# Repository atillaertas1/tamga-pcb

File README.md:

<p align="center">
  <picture>
    <source media="(prefers-color-scheme: dark)" srcset="assets/logo-dark.svg" />
    
  </picture>
</p>

<p align="center"><b>Describe a circuit. Get a routed, DRC-clean KiCad board and a JLCPCB order.</b></p>

<p align="center">
  
  &nbsp;
  
  &nbsp;
  
  &nbsp;
  
  &nbsp;
  
  &nbsp;
  
</p>

<p align="center"><sub>An ESP32-C3 board with USB-C, a 3.3 V regulator, reset/boot buttons and a GPIO header: schematic,
placement, routing, ground pour, DRC and fab files all made through tamga-pcb's tools.
<a href="examples/esp32c3-devboard">Rebuild it yourself</a>.</sub></p>

**tamga-pcb** gives Claude Code the whole KiCad workflow as 22 compact tools. You describe the board in plain
words; Claude writes a short circuit spec, tamga-pcb turns it into a schematic and a PCB, places the parts,
routes the board with Freerouting, pours ground, loops on DRC until it is clean, and exports Gerbers, BOM and
pick-and-place for JLCPCB. Every LCSC part is checked against its real pinout on the way, and Claude never reads
raw KiCad files: tools answer in one-line summaries, so a whole board fits comfortably in the context.

```
> Make me an ESP32-C3 board powered from USB-C, with reset and boot buttons, a user LED
  and a GPIO header. Keep it under 60 x 32 mm and get it ready for JLCPCB.
```

## Examples

<table>
  <tr>
    <td width="50%" align="center"></td>
    <td width="50%" align="center"></td>
  </tr>
  <tr>
    <td><b><a href="examples/ch340-usb-uart">CH340C USB-C to UART adapter</a></b><br/><sub>Made by Claude Code from <b>one
    prompt</b>, unattended: 35 × 20 mm, DRC clean, fab files. <b>3 min, 48 tool calls, about $0.51</b> with Sonnet 5.5,
    measured. <a href="examples/ch340-usb-uart/SESSION.md">Session report</a></sub></td>
    <td><b><a href="examples/esp32c3-devboard">ESP32-C3 USB-C dev board</a></b><br/><sub>60 × 32 mm, 19 parts, reset/boot,
    native USB. Rebuilt end to end by a script through the same tools; the reference for the images above.</sub></td>
  </tr>
</table>

Token counts, cost, time and what the first attempt taught us: [docs/BENCHMARKS.md](docs/BENCHMARKS.md). On the same prompt with the same model, the most-starred KiCad MCP server also finished the board; tamga-pcb used 48 % less money, 43 % fewer tool calls and 40 % less peak context (one run each, [details](docs/BENCHMARKS.md#against-another-kicad-mcp-server)).

## Watch it live

Say *"I want to watch"* and Claude calls `live_view`: a page opens in your browser and redraws the board and the
schematic after every step, with each tool call, how long it took and what it found, and the DRC status on top.
It runs locally, needs no KiCad window, and costs no tokens: none of it goes back to Claude. From a terminal:
`uv run tamga watch` follows whatever project Claude is working on.

<p align="center"><sub>Replay of a real, unattended session: one prompt (an ATtiny85 board with USB-C, LDO, ISP header and
three LEDs, rounded corners, mounting holes), 59 tool calls, 5½ minutes, $0.68 with Sonnet 5.5. Every frame is one of
the session's own board states, made with <a href="scripts/replay_gif.py"><code>scripts/replay_gif.py</code></a>.</sub></p>

## Install

Run this inside Claude Code:

```
/plugin install tamga-pcb --marketplace atillaertas1/tamga-pcb
```

You need **[KiCad 10](https://www.kicad.org/download/)** and **[uv](https://docs.astral.sh/uv/)**; autorouting
also needs **Java 25+**. tamga-pcb finds KiCad on its own on Linux, macOS and Windows, builds its Python
environment on first start and downloads Freerouting the first time it routes. No API keys.

<details>
<summary>Older Claude Code versions</summary>

```
/plugin marketplace add atillaertas1/tamga-pcb
/plugin install tamga-pcb@tamga-pcb
```

</details>

<details>
<summary>Other MCP clients</summary>

Clone the repo and register this as a stdio server:

```bash
uv run --directory /path/to/tamga-pcb --extra lcsc tamga
```

The design workflow the plugin loads as a skill lives in [`skills/pcb-design/SKILL.md`](skills/pcb-design/SKILL.md);
give it to your agent as instructions.

</details>

<details>
<summary>Something not found?</summary>

Ask Claude to *run the tamga doctor*. It checks KiCad, its Python, the libraries, Java and the network, and names the
environment variable to set for anything it cannot find: `TAMGA_KICAD_CLI`, `TAMGA_KICAD_PYTHON`,
`TAMGA_SYMBOL_DIR`, `TAMGA_FOOTPRINT_DIR`, `TAMGA_JAVA`, `FREEROUTING_JAR`.

</details>

## From a spec to a board

The single source of truth is a short `<name>.circuit.json`: parts, footprints, LCSC numbers and which net each
pin goes to. Claude writes it, tamga-pcb does the rest.

```json
{"ref": "U2", "symbol": "RF_Module:ESP32-C3-WROOM-02", "lcsc": "C2934560",
 "footprint": "RF_Module:ESP32-C3-WROOM-02", "sheet": "MCU",
 "pins": {"1": "+3V3", "2": "EN", "13": "USB_DN", "14": "USB_DP", "9": "GND"}}
```

<table>
  <tr>
    <td width="50%"></td>
    <td width="50%"></td>
  </tr>
  <tr>
    <td align="center"><sub>Generated schematic, one sheet per function</sub></td>
    <td align="center"><sub>Autorouted copper before the ground pour</sub></td>
  </tr>
</table>

## How it works

1. **Spec → schematic.** `sync_design` writes the `.kicad_sch` (functional sheets, power symbols, notes,
   deterministic UUIDs), exports the netlist with `kicad-cli` and checks it against the spec. A wrong pin name or a
   missing pad writes nothing and lists the valid pins.
2. **Check the real parts.** Each LCSC number is compared with the part's EasyEDA pinout. A swapped LED or the wrong
   symbol variant shows up here, not on the assembled board.
3. **Schematic → PCB.** The board is updated from the netlist like KiCad's *Update PCB*, keeping placement, then ERC
   and a schematic↔PCB parity check run.
4. **Place and route.** Claude places the parts in one batch, widens power nets with netclasses, hand-routes critical
   nets with `route_net` (locked), and lets Freerouting route the rest headlessly.
5. **Pour and verify.** A two-layer ground pour with stitching vias, then `run_drc` until it says `CLEAN`, with the
   violations grouped by type and located.
6. **Order.** `export_fab` writes Gerbers, drill files, a BOM and a CPL in JLCPCB's format and lists parts without an
   LCSC code.

The [pcb-design skill](skills/pcb-design/SKILL.md) carries the loop, the placement checklist and JLCPCB's limits, so
Claude follows the same steps every time.

## The tools

| Tool | What it does |
| --- | --- |
| `sync_design` | Spec → schematic + PCB, netlist and pinout checks, ERC, parity. Edits go through small patches. |
| `find_symbol`, `get_symbol`, `find_footprint` | Search KiCad's libraries; confirm pin names and that footprint pads match. |
| `search_parts`, `import_lcsc_part` | JLCPCB/LCSC stock and price, basic parts first, passives by value; bring in parts KiCad doesn't have. |
| `create_part` | Footprint and symbol from a datasheet when neither KiCad nor LCSC has the part: SOIC/TSSOP/MSOP, QFN/DFN, headers, custom pads. |
| `board_summary`, `get_footprint` | One line per footprint and net, pad positions, routed lengths and pair skew. No raw `.kicad_pcb` in the context. |
| `place_footprints` | Move, rotate and flip many footprints in one call. |
| `set_netclass`, `route_net` | Track widths per net class, sized from a target impedance; guided, locked routes and differential pairs. |
| `autoroute` | Freerouting without its GUI, with progress and a timeout that reports where it stopped. |
| `add_copper_zone`, `fill_zones` | Ground pours with stitching vias. |
| `run_drc`, `run_erc` | Violations grouped by type with example locations: 300 violations fit in about 1 KB. |
| `render_board` | PNG of the board for a visual check. |
| `live_view` | Opens the live page for the user (above); nothing comes back to Claude. |
| `export_fab` | Gerbers, drill, BOM and CPL for JLCPCB; optional schematic PDF, STEP, ODB++, IPC-2581 and a parts-cost summary. |
| `import_board` | Bring in Altium, Eagle, PADS or CADSTAR boards. |

## Why it is cheap on tokens

| Choice | Effect |
| --- | --- |
| 22 tools with short descriptions | all tool schemas together ≈ 4.2k tokens (16.7k characters, measured) |
| Small answers | in the [CH340 run](examples/ch340-usb-uart/SESSION.md) all 48 tool results together were ≈ 4.2k tokens, about 350 characters per call |
| No raw KiCad files, one line per footprint | a 7-part board summary is about 900 characters |
| DRC/ERC grouped by type, three example locations | 300 violations → about 1 KB |
| Workflow in a skill | loaded only when you work on a PCB |

## Under the hood

- **pcbnew runs in a worker process** in KiCad's own Python; it can crash without taking the server down.
- **File based**, not KiCad's IPC API: it works without the KiCad window open, and in CI.
- **Freerouting through pcbnew's DSN/SES export**, because `kicad-cli` 10 has none.
- **Self-contained projects:** non-stock libraries are copied into `<project>/lib/`, so a project folder can be zipped
  and shared as is.

## Development

```bash
git clone https://github.com/atillaertas1/tamga-pcb && cd tamga-pcb
uv sync --extra lcsc
uv run pytest -q          # KiCad-dependent tests are skipped when KiCad is not installed
claude --plugin-dir .     # run Claude Code with your working copy as the plugin
```

The example board is rebuilt end to end by `uv run python examples/esp32c3-devboard/build.py`. Changes are listed in
the [changelog](CHANGELOG.md). Want to help? See [CONTRIBUTING.md](CONTRIBUTING.md) and the
[good first issues](https://github.com/atillaertas1/tamga-pcb/labels/good%20first%20issue).

## Roadmap

- [ ] Live editing in an open KiCad through its IPC API
- [ ] Hierarchical pins on sheet symbols, tidier power-sheet layout
- [ ] Alternative routers (DeepPCB, Quilter)
- [ ] ngspice simulation of analog blocks

## The name

A *tamga* is the seal Turkic clans stamped onto stone, metal and coins: a mark pressed permanently into a surface,
much like a circuit etched into copper.

## License

MIT, see [LICENSE](LICENSE). **The boards you make are entirely yours**; no tool's license carries over to its output.
Optional parts are installed separately under their own licenses: easyeda2kicad (AGPL-3.0, the `lcsc` extra, run as a
separate process) and Freerouting (GPL-3.0, a separate jar downloaded on first use). KiCad is GPL-3.0.

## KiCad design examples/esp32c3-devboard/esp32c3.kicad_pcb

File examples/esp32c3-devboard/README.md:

# ESP32-C3 USB-C dev board

A 60 × 32 mm, two-layer board made entirely through tamga-pcb's tools, the same calls Claude makes:

- **USB-C** sink (5.1 kΩ on CC1/CC2), native USB to the ESP32-C3 (IO18 = D−, IO19 = D+)
- **AMS1117-3.3** regulator with input/output capacitors and a power LED
- **ESP32-C3-WROOM-02** module, antenna flush with the board edge
- **Reset and boot** buttons, EN RC delay, IO2/IO8/IO9 strapping
- **10-pin header:** 3V3, GND, UART and five GPIOs, plus VBUS

Every part has a JLCPCB/LCSC number except the header (`missing_lcsc: J2`).

## Files

| File | What it is |
| --- | --- |
| [`esp32c3.circuit.json`](esp32c3.circuit.json) | The spec: the only file written by hand (by Claude) |
| `esp32c3*.kicad_sch` | Generated schematic: Power, MCU and IO sheets |
| `esp32c3.kicad_pcb` | Placed, routed, poured and DRC-clean board |
| [`build.py`](build.py) | Rebuilds everything above from the spec and renders the README images |

## Rebuild

From the repo root, with KiCad 10, Java 25+ and `uv sync --extra lcsc` done:

```bash
uv run python examples/esp32c3-devboard/build.py
```

It runs `sync_design → place_footprints → set_netclass → autoroute → add_copper_zone → run_drc → export_fab`
and stops if DRC is not clean. Freerouting is not deterministic, so the tracks differ from run to run; DRC is clean
either way. The fab package lands in `fab/` (Gerber zip, BOM.csv, CPL.csv).

Two things worth knowing:

- KiCad ships no 3D body for the HRO TYPE-C-31-M-12 USB-C connector, so the render borrows the GCT USB4105 body,
  which has the same outline and locating holes. This only affects the picture.
- `pinout_warnings` from `sync_design` for J1, U1 and the buttons are naming differences between KiCad and EasyEDA
  (merged `A1B12` pins, the regulator tab, the switch's extra pins). The check exists for the real mistakes: on the
  first try it caught a red LED whose LCSC part has pad 1 as the anode while KiCad's footprint has it as the
  cathode, and that LED was swapped for one that matches.

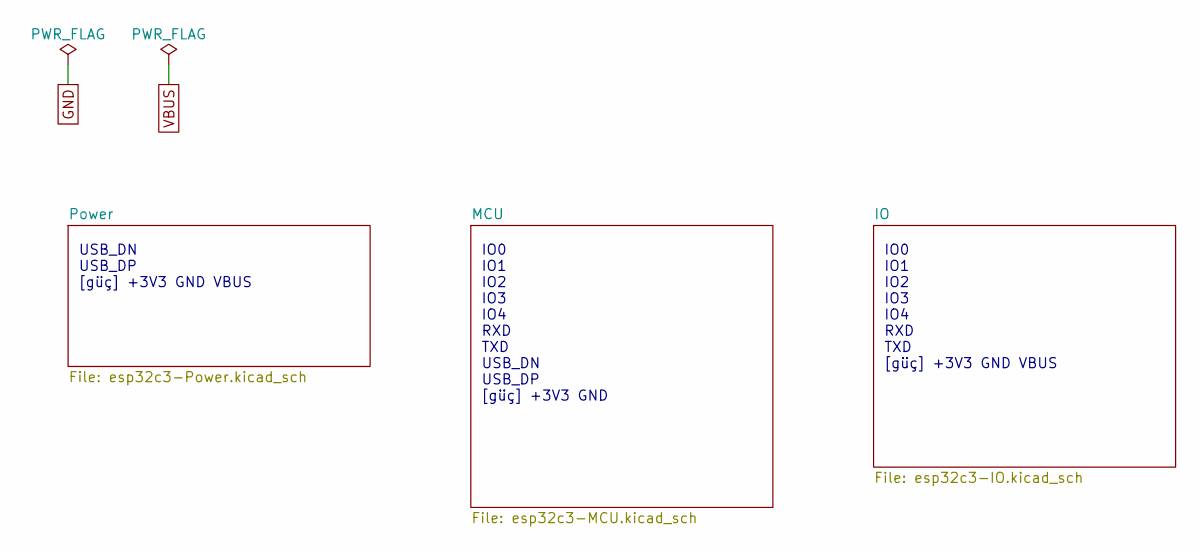
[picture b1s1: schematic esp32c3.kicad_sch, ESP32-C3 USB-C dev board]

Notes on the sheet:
USB_DN USB_DP [güç] +3V3 GND VBUS
IO0 IO1 IO2 IO3 IO4 RXD TXD USB_DN USB_DP [güç] +3V3 GND
IO0 IO1 IO2 IO3 IO4 RXD TXD [güç] +3V3 GND VBUS

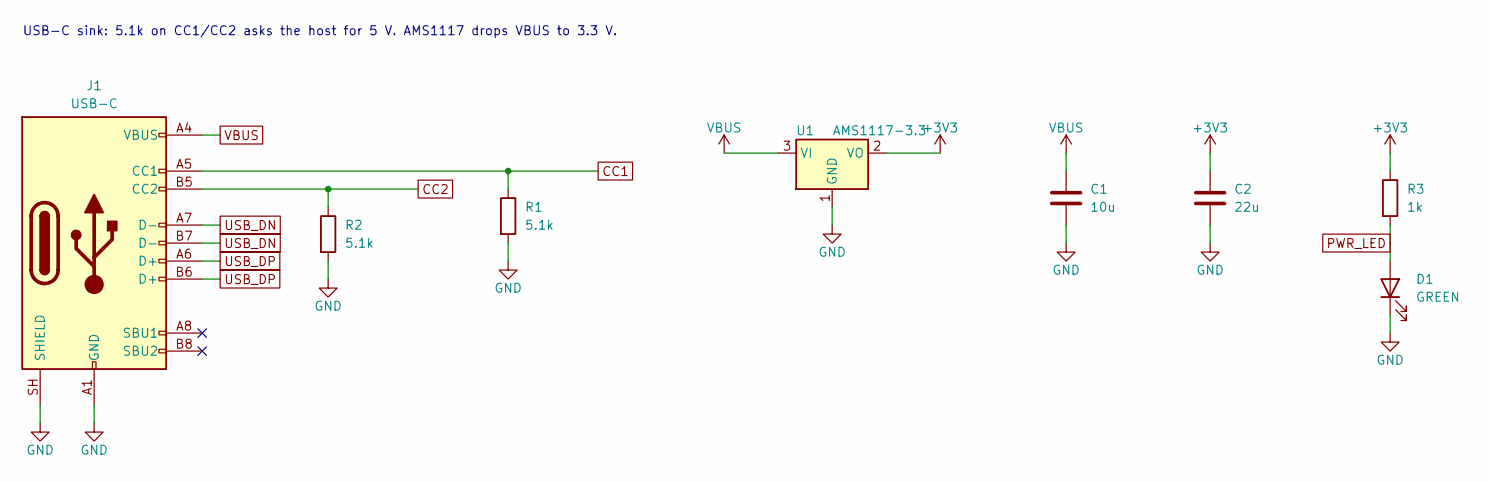
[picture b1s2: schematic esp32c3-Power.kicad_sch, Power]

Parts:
C1: 10u; C_0805_2012Metric; LCSC C15850
C2: 22u; C_0805_2012Metric; LCSC C45783
D1: GREEN; LED_0603_1608Metric; LCSC C72043
J1: USB-C; USB_C_Receptacle_HRO_TYPE-C-31-M-12; LCSC C165948
R1, R2: 5.1k; R_0603_1608Metric; LCSC C23186
R3: 1k; R_0603_1608Metric; LCSC C21190
U1: AMS1117-3.3; SOT-223-3_TabPin2; LCSC C6186

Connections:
+3V3: C2.1, R3.1, U1.2 (VO); also elsewhere on the board
CC1: J1.A5 (CC1), R1.1
CC2: J1.B5 (CC2), R2.1
GND: C1.2, C2.2, D1.1 (K), J1.A1 (GND), J1.A12 (GND), J1.B1 (GND), J1.B12 (GND), J1.SH (SHIELD), R1.2, R2.2, U1.1 (GND); also elsewhere on the board
PWR_LED: D1.2 (A), R3.2
USB_DN: J1.A7 (D-), J1.B7 (D-); also elsewhere on the board
USB_DP: J1.A6 (D+), J1.B6 (D+); also elsewhere on the board
VBUS: C1.1, J1.A4 (VBUS), J1.A9 (VBUS), J1.B4 (VBUS), J1.B9 (VBUS), U1.3 (VI); also elsewhere on the board

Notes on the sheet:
USB-C sink: 5.1k on CC1/CC2 asks the host for 5 V. AMS1117 drops VBUS to 3.3 V.

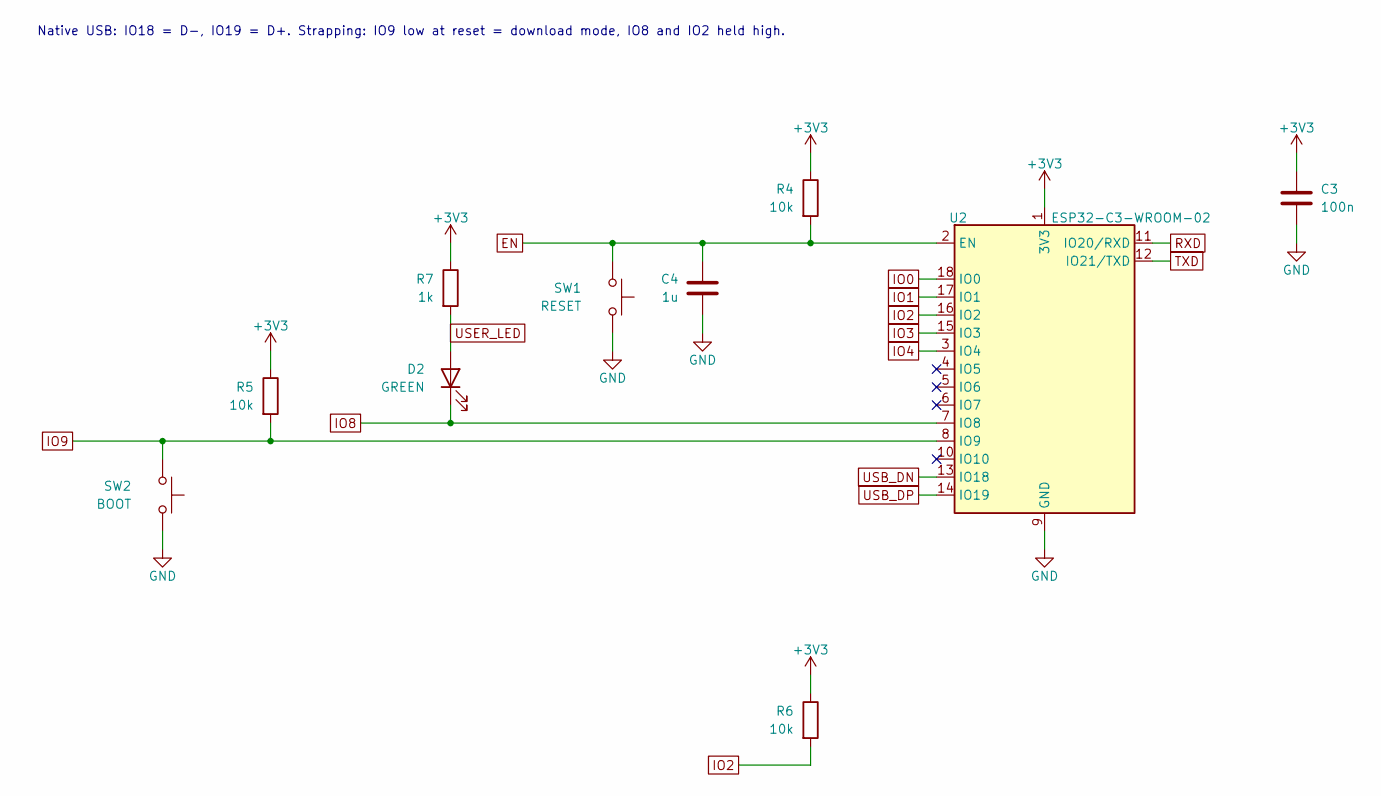
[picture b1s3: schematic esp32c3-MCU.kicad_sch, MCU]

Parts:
C3: 100n; C_0603_1608Metric; LCSC C14663
C4: 1u; C_0603_1608Metric; LCSC C15849
D2: GREEN; LED_0603_1608Metric; LCSC C72043
R4, R5, R6: 10k; R_0603_1608Metric; LCSC C25804
R7: 1k; R_0603_1608Metric; LCSC C21190
SW1: RESET; SW_SPST_TL3342; LCSC C318884
SW2: BOOT; SW_SPST_TL3342; LCSC C318884
U2: ESP32-C3-WROOM-02; LCSC C2934560

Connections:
+3V3: C3.1, R4.1, R5.1, R6.1, R7.1, U2.1 (3V3); also elsewhere on the board
EN: C4.1, R4.2, SW1.1, U2.2 (EN)
GND: C3.2, C4.2, SW1.2, SW2.2, U2.9 (GND), U2.19 (GND); also elsewhere on the board
IO0: U2.18 (IO0); also elsewhere on the board
IO1: U2.17 (IO1); also elsewhere on the board
IO2: R6.2, U2.16 (IO2); also elsewhere on the board
IO3: U2.15 (IO3); also elsewhere on the board
IO4: U2.3 (IO4); also elsewhere on the board
IO8: D2.1 (K), U2.7 (IO8)
IO9: R5.2, SW2.1, U2.8 (IO9)
RXD: U2.11 (IO20/RXD); also elsewhere on the board
TXD: U2.12 (IO21/TXD); also elsewhere on the board
USB_DN: U2.13 (IO18); also elsewhere on the board
USB_DP: U2.14 (IO19); also elsewhere on the board
USER_LED: D2.2 (A), R7.2

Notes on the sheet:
Native USB: IO18 = D-, IO19 = D+. Strapping: IO9 low at reset = download mode, IO8 and IO2 held high.

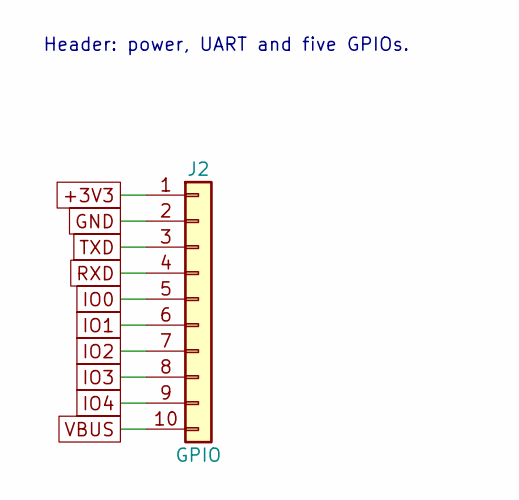
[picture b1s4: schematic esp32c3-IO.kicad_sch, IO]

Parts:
J2: GPIO; PinHeader_1x10_P2.54mm_Vertical

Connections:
+3V3: J2.1; also elsewhere on the board
GND: J2.2; also elsewhere on the board
IO0: J2.5; also elsewhere on the board
IO1: J2.6; also elsewhere on the board
IO2: J2.7; also elsewhere on the board
IO3: J2.8; also elsewhere on the board
IO4: J2.9; also elsewhere on the board
RXD: J2.4; also elsewhere on the board
TXD: J2.3; also elsewhere on the board
VBUS: J2.10; also elsewhere on the board

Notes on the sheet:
Header: power, UART and five GPIOs.

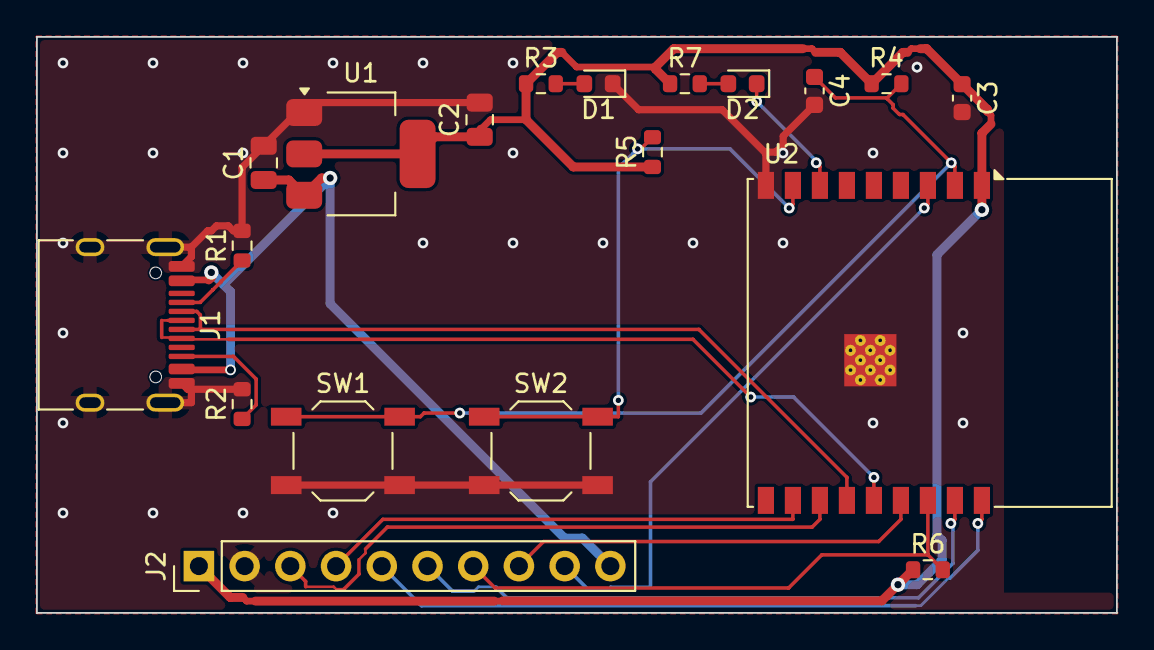
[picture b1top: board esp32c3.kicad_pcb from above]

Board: 2 copper layers, 60.0 x 32.0 mm, 19 parts (0 on the bottom side), 19 nets.

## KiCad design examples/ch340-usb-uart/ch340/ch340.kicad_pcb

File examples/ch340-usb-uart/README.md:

# CH340C USB-C to UART adapter

Made by Claude Code from **one prompt** ([`PROMPT.txt`](PROMPT.txt)), with no help along the way: 35 × 20 mm, two
layers, CH340C, USB-C, TX/RX LEDs and an FTDI-style 6-pin header. DRC clean, Gerbers, BOM and CPL exported.
**3 minutes, about $0.51** with `claude-sonnet-5-5`. The full measured report, with token charts and every tool call,
is in [SESSION.md](SESSION.md); the comparison with the first attempt is in [docs/BENCHMARKS.md](../../docs/BENCHMARKS.md).

## Files

| File | What it is |
| --- | --- |
| [`PROMPT.txt`](PROMPT.txt) | The prompt, verbatim |
| [`APPENDED_INSTRUCTION.txt`](APPENDED_INSTRUCTION.txt) | Added to the system prompt so the run is unattended (see SESSION.md) |
| [`ch340/ch340.circuit.json`](ch340/ch340.circuit.json) | The spec Claude wrote |
| `ch340/ch340.kicad_sch`, `ch340/ch340.kicad_pcb` | Generated schematic and the routed, poured board |
| [`SESSION.md`](SESSION.md), [`session-metrics.json`](session-metrics.json) | Measured report and raw numbers |
| [`first-attempt-metrics.json`](first-attempt-metrics.json) | The run that found two bugs, before they were fixed |

The schematic was regenerated once after the run, when the generator learned to use labels for power pins on crowded
connectors; the board, the spec and all numbers are the session's own.

Before ordering, Claude itself asks you to check two things in JLC's viewer: the LED polarity (the LCSC part numbers
its pads the other way round from KiCad's LED symbol, which `sync_design` also warns about) and the CPL rotations.

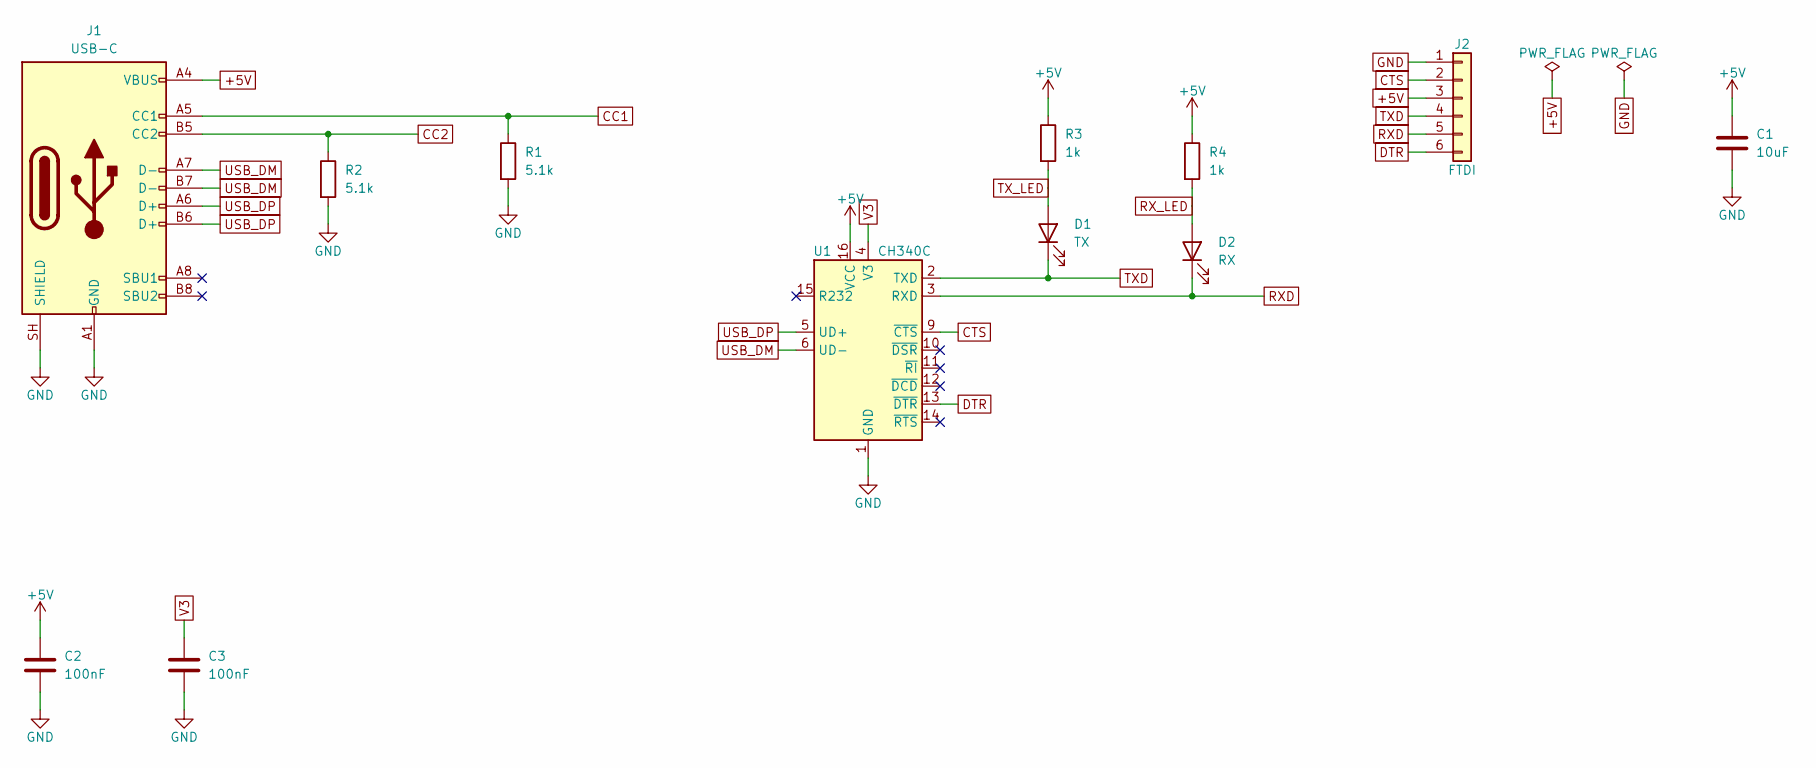
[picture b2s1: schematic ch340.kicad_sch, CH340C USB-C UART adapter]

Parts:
C1: 10uF; C_0805_2012Metric; LCSC C15850
C2, C3: 100nF; C_0603_1608Metric; LCSC C14663
D1: TX; LED_0603_1608Metric; LCSC C2286
D2: RX; LED_0603_1608Metric; LCSC C2286
J1: USB-C; USB_C_Receptacle_HRO_TYPE-C-31-M-12; LCSC C165948
J2: FTDI; PinHeader_1x06_P2.54mm_Vertical
R1, R2: 5.1k; R_0603_1608Metric; LCSC C23186
R3, R4: 1k; R_0603_1608Metric; LCSC C21190
U1: CH340C; SOIC-16_3.9x9.9mm_P1.27mm; LCSC C84681

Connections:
+5V: C1.1, C2.1, J1.A4 (VBUS), J1.A9 (VBUS), J1.B4 (VBUS), J1.B9 (VBUS), J2.3, R3.1, R4.1, U1.16 (VCC)
CC1: J1.A5 (CC1), R1.1
CC2: J1.B5 (CC2), R2.1
CTS: J2.2, U1.9 (~CTS)
DTR: J2.6, U1.13 (~DTR)
GND: C1.2, C2.2, C3.2, J1.A1 (GND), J1.A12 (GND), J1.B1 (GND), J1.B12 (GND), J1.SH (SHIELD), J2.1, R1.2, R2.2, U1.1 (GND)
RXD: D2.1 (K), J2.5, U1.3 (RXD)
RX_LED: D2.2 (A), R4.2
TXD: D1.1 (K), J2.4, U1.2 (TXD)
TX_LED: D1.2 (A), R3.2
USB_DM: J1.A7 (D-), J1.B7 (D-), U1.6 (UD-)
USB_DP: J1.A6 (D+), J1.B6 (D+), U1.5 (UD+)
V3: C3.1, U1.4 (V3)

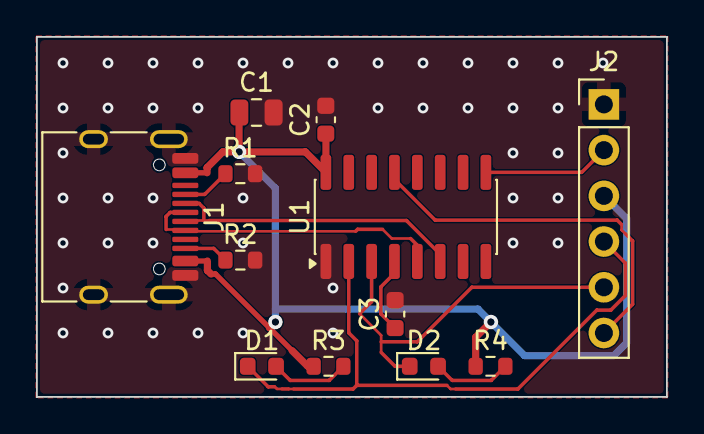
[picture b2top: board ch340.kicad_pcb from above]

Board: 2 copper layers, 35.0 x 20.0 mm, 12 parts (0 on the bottom side), 13 nets.

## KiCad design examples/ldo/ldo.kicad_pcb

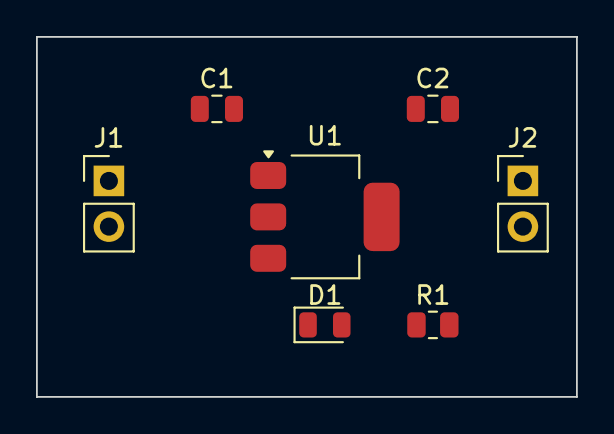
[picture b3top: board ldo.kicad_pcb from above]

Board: 2 copper layers, 30.0 x 20.0 mm, 7 parts (0 on the bottom side), 4 nets, no tracks yet.

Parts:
C1: 10u; C_0805_2012Metric
C2: 22u; C_0805_2012Metric
D1: GREEN; LED_0805_2012Metric
J1: VIN; PinHeader_1x02_P2.54mm_Vertical
J2: 3V3; PinHeader_1x02_P2.54mm_Vertical
R1: 1k; R_0805_2012Metric
U1: AMS1117-3.3; SOT-223-3_TabPin2

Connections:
+3V3: C2.1, J2.1, R1.1, U1.2
GND: C1.2, C2.2, D1.1, J1.2, J2.2, U1.1
LED_A: D1.2, R1.2
VIN: C1.1, J1.1, U1.3

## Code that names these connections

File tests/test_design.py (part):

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         "footprint": "Connector_PinHeader_2.54mm:PinHeader_1x02_P2.54mm_Vertical",
         "pins": {"1": "+5V", "2": "GND"}},
        {"ref": "R1", "symbol": "Device:R", "value": "330", "lcsc": "C17630",
         "footprint": "Resistor_SMD:R_0805_2012Metric", "pins": {"1": "+5V", "2": "LED_A"}},
        {"ref": "D1", "symbol": "Device:LED", "value": "GREEN",
         "footprint": "LED_SMD:LED_0805_2012Metric", "pins": {"A": "LED_A", "K": "GND"}},
    ],
}

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
def test_unconnected_pin_is_reported_by_erc(tmp_path):
    spec = json.loads(json.dumps(LED_SPEC))
    spec["parts"][2]["pins"] = {"A": "LED_A"}  # katot bağlı değil
    r = design.sync(str(tmp_path), "led", spec, None)
    assert r["erc"] != "CLEAN"
    assert any(t["type"] == "pin_not_connected" for t in r["erc"]["types"])
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    assert {f.name for f in tmp_path.glob("*.kicad_sch")} == {"led.kicad_sch", "led-Giris.kicad_sch", "led-LED_Bolumu.kicad_sch"}
    page = (tmp_path / "led-LED_Bolumu.kicad_sch").read_text()
    assert '(lib_id "power:GND")' in page and '(lib_id "power:+5V")' in page
    assert '(global_label "GND"' not in page and '(global_label "LED_A"' in page  # sinyal neti etiket kalır
    assert "330R" in page  # not sayfada
    root = (tmp_path / "led.kicad_sch").read_text()
    assert '"Sheetname" "LED Bölümü"' in root and "[güç] +5V GND" in root  # kök: sayfalar arası arayüz
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

DP_SPEC = {"title": "DP", "board": {"width_mm": 40, "height_mm": 20, "layers": 4}, "parts": [
    {"ref": "J1", "symbol": "Connector_Generic:Conn_01x04", "pins": {"1": "VBUS", "2": "USB_DP", "3": "USB_DN", "4": "GND"},
     "footprint": "Connector_PinHeader_2.54mm:PinHeader_1x04_P2.54mm_Vertical"},
    {"ref": "J2", "symbol": "Connector_Generic:Conn_01x04", "pins": {"1": "VBUS", "2": "USB_DP", "3": "USB_DN", "4": "GND"},
     "footprint": "Connector_PinHeader_2.54mm:PinHeader_1x04_P2.54mm_Vertical"}]}


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

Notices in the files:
README.md:
MIT License
